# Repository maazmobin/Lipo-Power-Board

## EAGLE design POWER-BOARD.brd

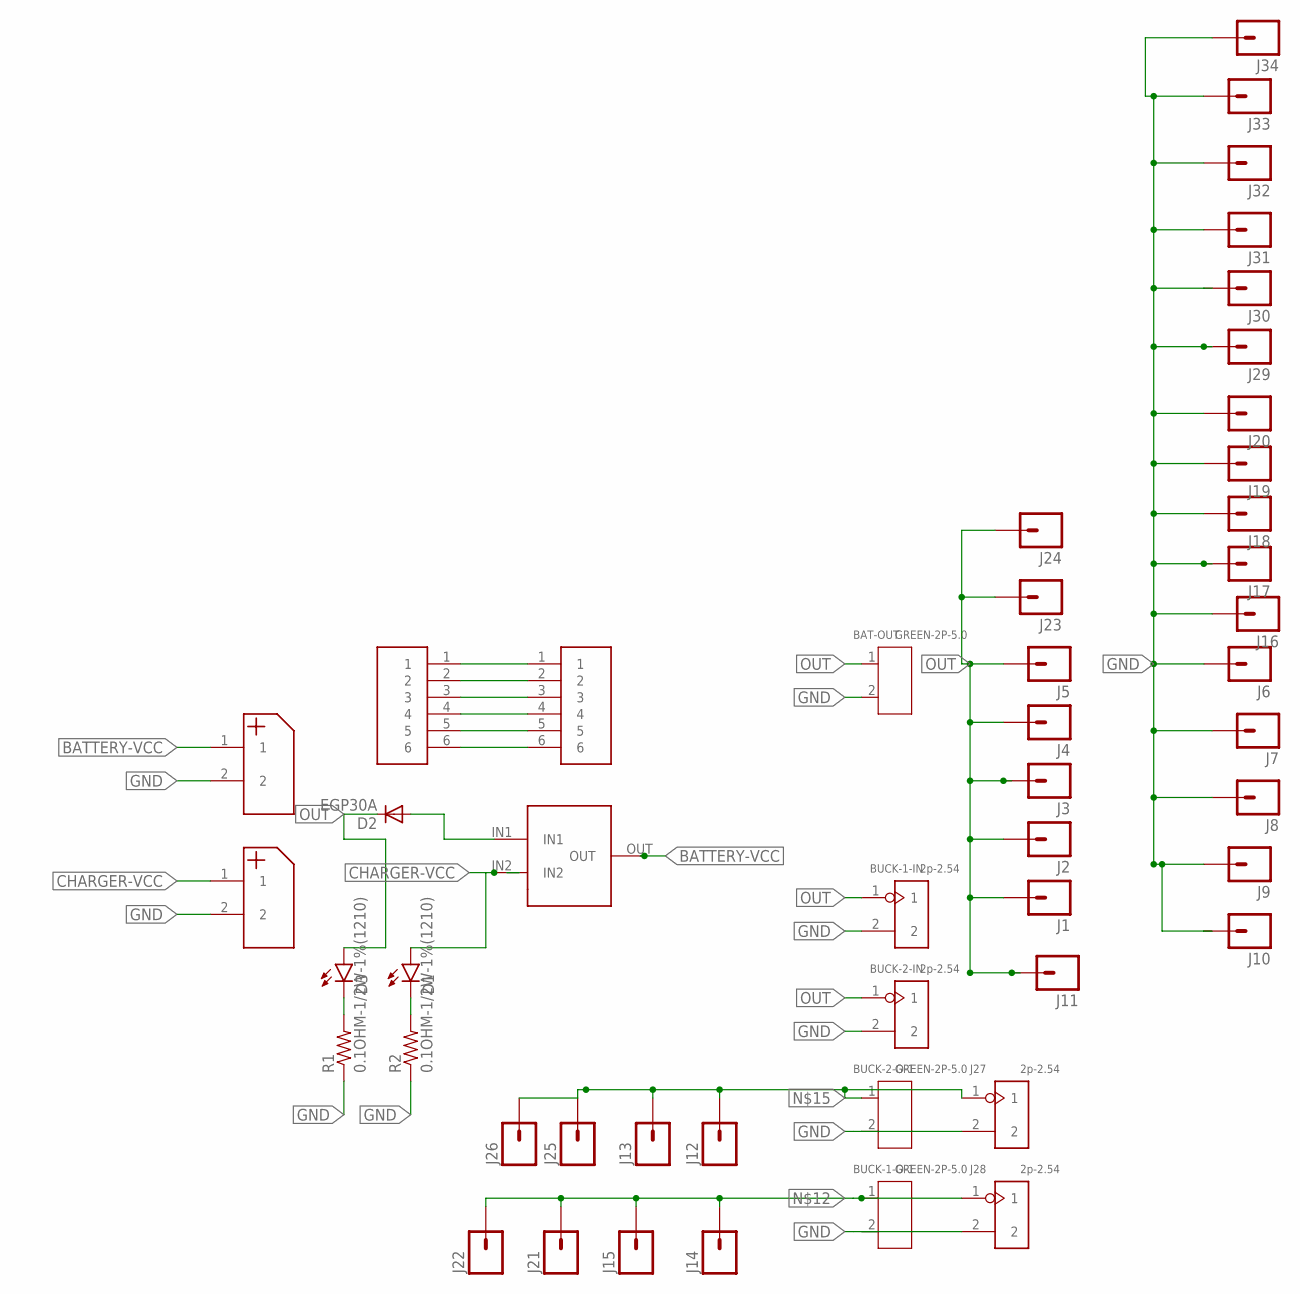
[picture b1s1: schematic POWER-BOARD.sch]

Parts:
BAT-OUT: GREEN-2P-5.0; H2-5.0-10.5X8.0MM
BUCK-1-IN, BUCK-2-IN: 2p-2.54; H2-2.54
BUCK-1-O-1, BUCK-2-O-1: GREEN-2P-5.0; H2-5.0-10.5X8.0MM
D1, D3: LED-FKIT-1206; FKIT-LED-1206
D2: EGP30A; DO201-15
J1, J2, J3, J4, J5, J6, J7, J8, J9, J10, J11, J12, J13, J14, J15, J16, J17, J18, J19, J20, J21, J22, J23, J24, J25, J26, J29, J30, J31, J32, J33, J34: M01PTH; 1X01
J27, J28: 2p-2.54; H2-2.54
R1, R2: 0.1OHM-1/2W-1%(1210); 1210
U$1: SPDT; SWITCH
U$2, U$3: LIPO-POWER
U$4, U$5: LIPO-CHARGING; CHARGING-CONN

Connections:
BATTERY-VCC: U$1.OUT, U$2.1
CHARGER-VCC: D1.A, U$1.IN2, U$3.1
GND: BAT-OUT.2, BUCK-1-IN.2, BUCK-1-O-1.2, BUCK-2-IN.2, BUCK-2-O-1.2, J6.1, J7.1, J8.1, J9.1, J10.1, J16.1, J17.1, J18.1, J19.1, J20.1, J27.2, J28.2, J29.1, J30.1, J31.1, J32.1, J33.1, J34.1, R1.1, R2.1, U$2.2, U$3.2
unnamed: D2.A, U$1.IN1
unnamed: D3.C, R1.2
unnamed: D1.C, R2.2
unnamed: U$4.1, U$5.1
unnamed: U$4.2, U$5.2
unnamed: U$4.3, U$5.3
unnamed: U$4.4, U$5.4
unnamed: U$4.5, U$5.5
unnamed: U$4.6, U$5.6
unnamed: BUCK-1-O-1.1, J14.1, J15.1, J21.1, J22.1, J28.1
unnamed: BUCK-2-O-1.1, J12.1, J13.1, J25.1, J26.1, J27.1
OUT: BAT-OUT.1, BUCK-1-IN.1, BUCK-2-IN.1, D2.C, D3.A, J1.1, J2.1, J3.1, J4.1, J5.1, J11.1, J23.1, J24.1

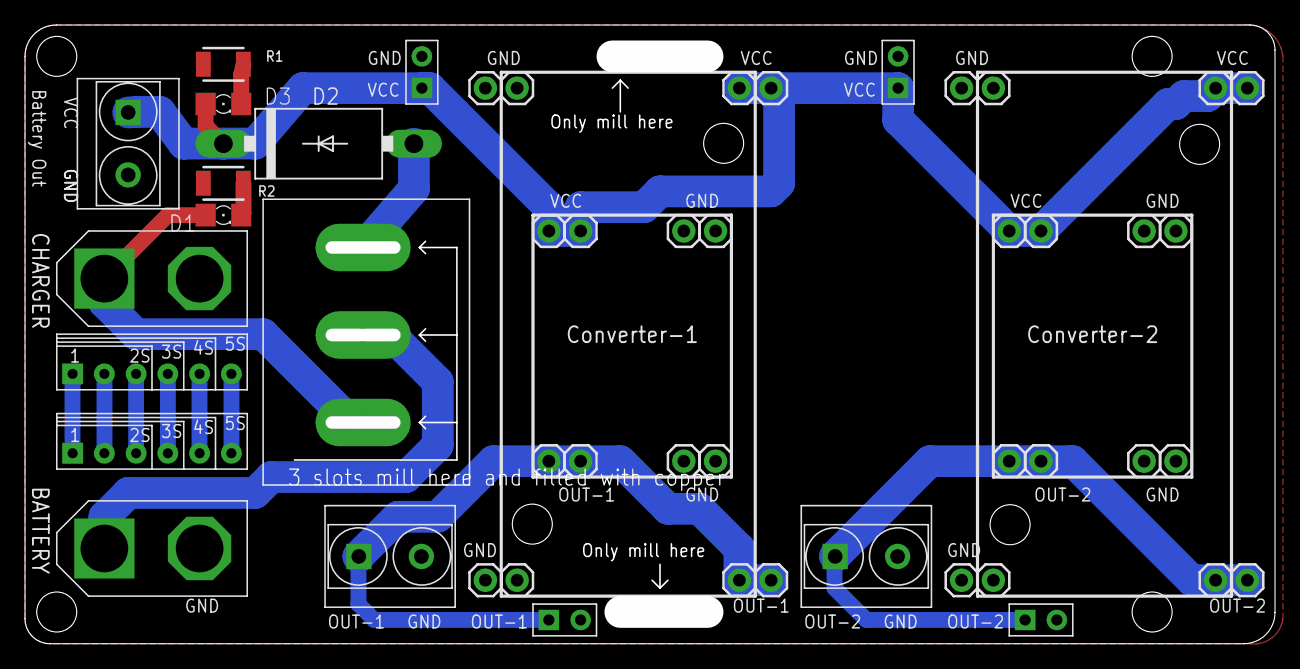
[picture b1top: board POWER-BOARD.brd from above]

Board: 2 copper layers, 100.0 x 49.5 mm, 49 parts (0 on the bottom side), 15 nets.

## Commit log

2016-12-14 :neckbeard: Added .gitattributes & .gitignore files
2016-12-14 Cosmetics required
2016-12-14 Font Edit

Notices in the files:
parts and their libraries:
SparkFun-Connectors: Licensing: Creative Commons ShareAlike 4.0 International - https://creativecommons.org/licenses/by-sa/4.0
